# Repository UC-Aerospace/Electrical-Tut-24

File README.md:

# 2024 Avionics tutorial example boards!!
Here's where you'll find basic examples of a flight computer board using the RP2040 microcontroller. 

We have two different example sizes.  
  
(50mm x 50mm) This shows it's possible to design a 2-layer 50mm x 50mm board to fit the minimum rocket tube diameter of 50mm. Made by Grayson. This is the one we have ordered and will be avalible to pass around.  
  
~~(66mm x 66mm) This 2-layer example board is slightly bigger but small enough to fit in an L2 rocket. Made by Kaden.~~  
Unfortunatly this board has some issues at the moment, we might look into fixing it. Left for now as it shows a different general approach.

> [!NOTE]
> While making a 2-layer 50mm x 50mm board is possible, routing something this small can be quite a puzzle especially to do nicely. If you do target 50x50 we would reccomend a 4-layer board. Otherwise, we'd suggest something either 66x66mm or 88x88mm.

> [!CAUTION]
> We are not experts and are still all learning a lot ourselves. As such some of these designs may be suboptimal, don't take them as best practice. If you see an issue with any of the boards, or even just think you do, feel free to create an issue so we can all learn.

## Templates

These are barebones files to use as a starting point, and very simply include a board outline with holes that will match with our sleds, the RP2040 footprint and the Sense module footprint. Avalible in 50x50, 66x66 and 88x88 to modify as you wish.

## Resources / Datasheets
**_Please look_** at the datasheets for any major components you plan to use, e.g. (Voltage regulator, RP2040, Flash chip, Screen, LEDs, USB-C connector, etc..) They provide the information necessary to integrate them with your project and if any extra components are needed to work correctly.

The Raspberry Pi Foundation has provided a massive amount of technical information for the RP2040 microcontroller we use, so I'd suggest reviewing their datasheets to help build your boards! They definitely helped me :) 

[RP2040 Datasheet](https://datasheets.raspberrypi.com/rp2040/rp2040-datasheet.pdf)  
[RP2040 Hardware design examples](https://datasheets.raspberrypi.com/rp2040/hardware-design-with-rp2040.pdf)  
[Raspberry Pi Pico datasheet](https://datasheets.raspberrypi.com/pico/pico-datasheet.pdf)
  
Also take a look at the sensor package used which we have got assembled for you:
[MicroSense](https://github.com/UC-Aerospace/Sense)

If you have any questions about the example board, then come talk to me!  
Happy making! (The first year Grayson) :3

^ Graysons demo flight computer, we will have a few to pass around.

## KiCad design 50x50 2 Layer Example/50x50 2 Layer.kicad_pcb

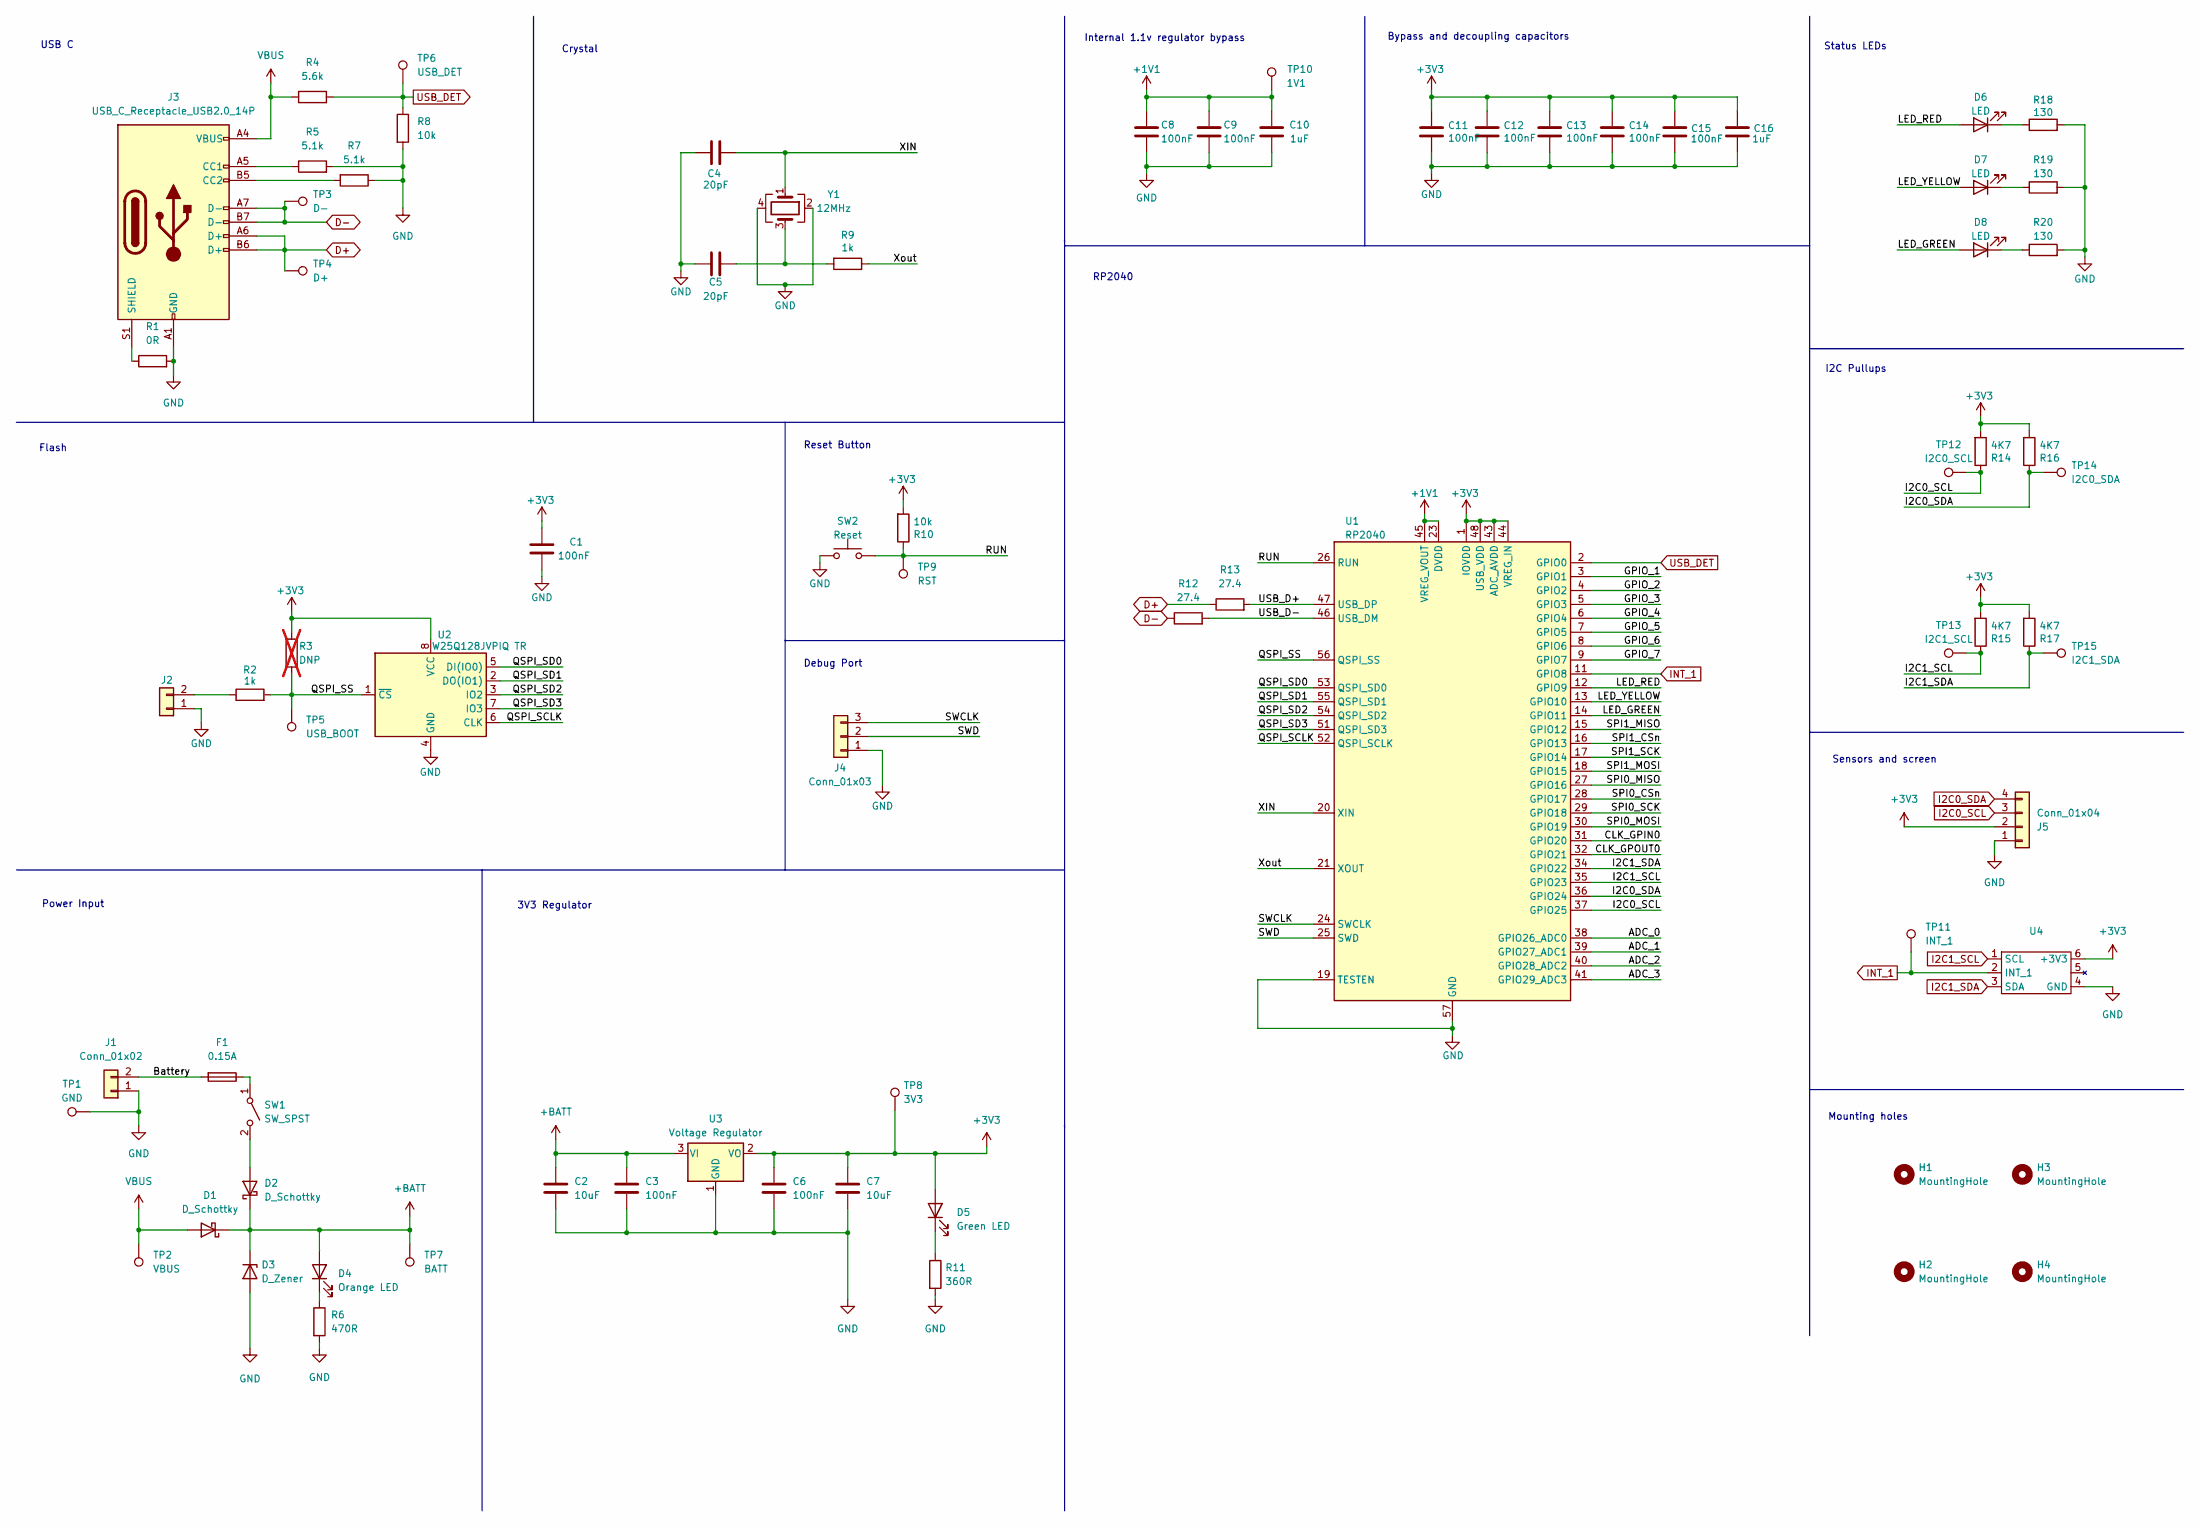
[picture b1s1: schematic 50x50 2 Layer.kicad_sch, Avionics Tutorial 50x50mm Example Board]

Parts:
C1, C8, C9, C11, C12, C13, C14: 100nF; C_0805_2012Metric_Pad1.18x1.45mm_HandSolder; MPN CL10B104KB8NNWC
C2, C7: 10uF; C_0805_2012Metric_Pad1.18x1.45mm_HandSolder; MPN CL21A106KOQNNNE
C3, C6: 100nF; C_0805_2012Metric_Pad1.18x1.45mm_HandSolder; MPN CL21B104KBCNNNC
C4, C5: 20pF; C_0805_2012Metric_Pad1.18x1.45mm_HandSolder; MPN 0603N270J500CT
C10, C16: 1uF; C_0805_2012Metric_Pad1.18x1.45mm_HandSolder; MPN CL10B105KA8NNNC
C15: 100nF; C_0805_2012Metric_Pad1.18x1.45mm_HandSolder; MPN CL10B105KA8NNNC
D1, D2: D_Schottky; D_SMA; MPN 4786-SK34ACT-ND
D3: D_Zener; D_SOD-123; MPN BZT52C12-TP
D4: Orange LED; LED_0603_1608Metric; MPN B1911UD--20D001014U1930
D5: Green LED; LED_0603_1608Metric; MPN B1931NG--20D001114U1930
D6: LED; LED_0402_1005Metric_Pad0.77x0.64mm_HandSolder; MPN 150040RS73240
D7: LED; LED_0402_1005Metric_Pad0.77x0.64mm_HandSolder; MPN 150040YS73240
D8: LED; LED_0402_1005Metric_Pad0.77x0.64mm_HandSolder; MPN 150040VS73240
F1: 0.15A; Fuse_0603_1608Metric; MPN FMC16302WHTP
H1, H2, H3, H4: MountingHole; MountingHole_3.2mm_M3
J1: Conn_01x02; JST_XH_B2B-XH-A_1x02_P2.50mm_Vertical; MPN S2B-XH-A(LF)(SN)
J2: Conn_01x02; PinHeader_1x02_P2.54mm_Vertical
J3: USB_C_Receptacle_USB2.0_14P; USB_C_Receptacle_GCT_USB4105-xx-A_16P_TopMnt_Horizontal
J4: Conn_01x03; PinSocket_1x03_P2.54mm_Vertical
J5: Conn_01x04; PinSocket_1x04_P2.54mm_Vertical
R1: 0R; R_0805_2012Metric_Pad1.20x1.40mm_HandSolder
R2, R9: 1k; R_0805_2012Metric_Pad1.20x1.40mm_HandSolder; MPN RMCF0603FT1K00
R3: DNP; R_0805_2012Metric_Pad1.20x1.40mm_HandSolder; not fitted
R4: 5.6k; R_0805_2012Metric_Pad1.20x1.40mm_HandSolder
R5, R7: 5.1k; R_0805_2012Metric_Pad1.20x1.40mm_HandSolder
R6: 470R; R_0805_2012Metric_Pad1.20x1.40mm_HandSolder; MPN RC0805JR-07360RL
R8: 10k; R_0805_2012Metric_Pad1.20x1.40mm_HandSolder
R10: 10k; R_0805_2012Metric_Pad1.20x1.40mm_HandSolder; MPN RMCF0603FT10K0
R11: 360R; R_0805_2012Metric_Pad1.20x1.40mm_HandSolder; MPN RC0805JR-07360RL
R12, R13: 27.4; R_0805_2012Metric_Pad1.20x1.40mm_HandSolder
R14, R15, R16, R17: 4K7; R_0805_2012Metric_Pad1.20x1.40mm_HandSolder; MPN RC0603FR-074K7L
R18, R19, R20: 130; R_0805_2012Metric_Pad1.20x1.40mm_HandSolder; MPN RC0603FR-07130RL
SW1: SW_SPST; JST_XH_B2B-XH-A_1x02_P2.50mm_Vertical; MPN S2B-XH-A(LF)(SN)
SW2: Reset; SW_SPST_PTS645; MPN PTS645SM43SMTR92 LFS
TP1: GND; TestPoint_Pad_1.0x1.0mm; MPN S1751-46R
TP2: VBUS; TestPoint_Pad_1.0x1.0mm; MPN S1751-46R
TP3: D-; TestPoint_Pad_1.0x1.0mm; MPN S1751-46R
TP4: D+; TestPoint_Pad_1.0x1.0mm; MPN S1751-46R
TP5: USB_BOOT; TestPoint_Pad_1.0x1.0mm; MPN S1751-46R
TP6: USB_DET; TestPoint_Pad_1.0x1.0mm; MPN S1751-46R
TP7: BATT; TestPoint_Pad_1.0x1.0mm; MPN S1751-46R
TP8: 3V3; TestPoint_Pad_1.0x1.0mm; MPN S1751-46R
TP9: RST; TestPoint_Pad_1.0x1.0mm; MPN S1751-46R
TP10: 1V1; TestPoint_Pad_1.0x1.0mm; MPN S1751-46R
TP11: INT_1; TestPoint_Pad_1.0x1.0mm; MPN S1751-46R
TP12: I2C0_SCL; TestPoint_Pad_1.0x1.0mm; MPN S1751-46R
TP13: I2C1_SCL; TestPoint_Pad_1.0x1.0mm; MPN S1751-46R
TP14: I2C0_SDA; TestPoint_Pad_1.0x1.0mm; MPN S1751-46R
TP15: I2C1_SDA; TestPoint_Pad_1.0x1.0mm; MPN S1751-46R
U1: RP2040; QFN-56-1EP_7x7mm_P0.4mm_EP3.2x3.2mm; MPN SC0914(13)
U2: W25Q128JVPIQ TR; SOIC-8_5.23x5.23mm_P1.27mm; MPN W25Q128JVPIQ TR
U3: Voltage Regulator; SOT-223; MPN BA033CC0FP-E2
U4: UCA_Sense
Y1: 12MHz; Crystal_SMD_3225-4Pin_3.2x2.5mm_HandSoldering

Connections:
+1V1: C8.1, C9.1, C10.2, TP10.1, U1.23 (DVDD), U1.45 (VREG_VOUT), U1.50 (DVDD)
+3V3: C1.2, C6.1, C7.1, C11.1, C12.1, C13.1, C14.1, C15.2, C16.2, D5.2 (A), J5.2, R3.1, R10.2, R14.2, R15.2, R16.2, R17.2, TP8.1, U1.1 (IOVDD), U1.10 (IOVDD), U1.22 (IOVDD), U1.33 (IOVDD), U1.42 (IOVDD), U1.43 (ADC_AVDD), U1.44 (VREG_IN), U1.48 (USB_VDD), U1.49 (IOVDD), U2.8 (VCC), U3.2 (VO), U4.6 (+3V3)
+BATT: C2.1, C3.1, D1.1 (K), D2.1 (K), D3.1 (K), D4.2 (A), TP7.1, U3.3 (VI)
/ADC_0: U1.38 (GPIO26_ADC0)
/ADC_1: U1.39 (GPIO27_ADC1)
/ADC_2: U1.40 (GPIO28_ADC2)
/ADC_3: U1.41 (GPIO29_ADC3)
/Battery: F1.2, J1.2
/CLK_GPIN0: U1.31 (GPIO20)
/CLK_GPOUT0: U1.32 (GPIO21)
/GPIO_1: U1.3 (GPIO1)
/GPIO_2: U1.4 (GPIO2)
/GPIO_3: U1.5 (GPIO3)
/GPIO_4: U1.6 (GPIO4)
/GPIO_5: U1.7 (GPIO5)
/GPIO_6: U1.8 (GPIO6)
/GPIO_7: U1.9 (GPIO7)
/LED_GREEN: D8.2 (A), U1.14 (GPIO11)
/LED_RED: D6.2 (A), U1.12 (GPIO9)
/LED_YELLOW: D7.2 (A), U1.13 (GPIO10)
/QSPI_SCLK: U1.52 (QSPI_SCLK), U2.6 (CLK)
/QSPI_SD0: U1.53 (QSPI_SD0), U2.5 (DI(IO0))
/QSPI_SD1: U1.55 (QSPI_SD1), U2.2 (DO(IO1))
/QSPI_SD2: U1.54 (QSPI_SD2), U2.3 (IO2)
/QSPI_SD3: U1.51 (QSPI_SD3), U2.7 (IO3)
/QSPI_SS: R2.2, R3.2, TP5.1, U1.56 (QSPI_SS), U2.1 (~CS)
/RUN: R10.1, SW2.2, TP9.1, U1.26 (RUN)
/SPI0_CSn: U1.28 (GPIO17)
/SPI0_MISO: U1.27 (GPIO16)
/SPI0_MOSI: U1.30 (GPIO19)
/SPI0_SCK: U1.29 (GPIO18)
/SPI1_CSn: U1.16 (GPIO13)
/SPI1_MISO: U1.15 (GPIO12)
/SPI1_MOSI: U1.18 (GPIO15)
/SPI1_SCK: U1.17 (GPIO14)
/SWCLK: J4.3, U1.24 (SWCLK)
/SWD: J4.2, U1.25 (SWD)
/USB_D+: R13.2, U1.47 (USB_DP)
/USB_D-: R12.2, U1.46 (USB_DM)
/XIN: C4.1, U1.20 (XIN), Y1.1
/Xout: R9.1, U1.21 (XOUT)
D+: J3.A6 (D+), J3.B6 (D+), R13.1, TP4.1
D-: J3.A7 (D-), J3.B7 (D-), R12.1, TP3.1
GND: C1.1, C2.2, C3.2, C4.2, C5.2, C6.2, C7.2, C8.2, C9.2, C10.1, C11.2, C12.2, C13.2, C14.2, C15.1, C16.1, D3.2 (A), J1.1, J2.1, J3.A1 (GND), J3.A12 (GND), J3.B1 (GND), J3.B12 (GND), J4.1, J5.1, R1.2, R5.2, R6.2, R7.1, R8.2, R11.2, R18.2, R19.2, R20.2, SW2.1, TP1.1, U1.19 (TESTEN), U1.57 (GND), U2.4 (GND), U3.1 (GND), U4.4 (GND), Y1.2, Y1.4
I2C0_SCL: J5.3, R14.1, TP12.1, U1.37 (GPIO25)
I2C0_SDA: J5.4, R16.1, TP14.1, U1.36 (GPIO24)
I2C1_SCL: R15.1, TP13.1, U1.35 (GPIO23), U4.1 (SCL)
I2C1_SDA: R17.1, TP15.1, U1.34 (GPIO22), U4.3 (SDA)
INT_1: TP11.1, U1.11 (GPIO8), U4.2 (INT_1)
unnamed: C5.1, R9.2, Y1.3
unnamed: D2.2 (A), SW1.2 (B)
unnamed: D4.1 (K), R6.1
unnamed: D5.1 (K), R11.1
unnamed: D6.1 (K), R18.1
unnamed: D7.1 (K), R19.1
unnamed: D8.1 (K), R20.1
unnamed: J2.2, R2.1
unnamed: J3.A5 (CC1), R5.1
unnamed: J3.B5 (CC2), R7.2
unnamed: J3.S1 (SHIELD), R1.1
unnamed: F1.1, SW1.1 (A)
USB_DET: R4.2, R8.1, TP6.1, U1.2 (GPIO0)
VBUS: D1.2 (A), J3.A4 (VBUS), J3.A9 (VBUS), J3.B4 (VBUS), J3.B9 (VBUS), R4.1, TP2.1

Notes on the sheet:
Sensors and screen
Debug Port
Mounting holes
Power Input
Crystal
I2C Pullups
Internal 1.1v regulator bypass
RP2040
3V3 Regulator
Flash
USB C
Status LEDs
Reset Button
Bypass and decoupling capacitors

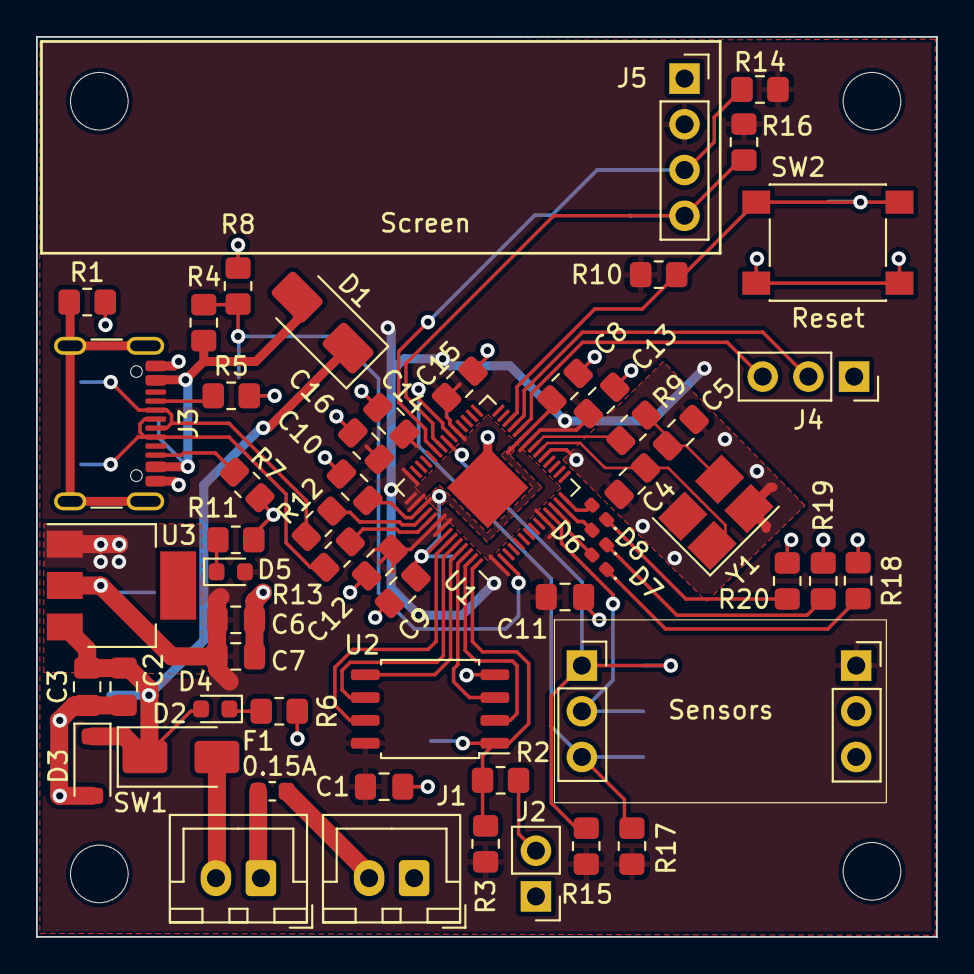
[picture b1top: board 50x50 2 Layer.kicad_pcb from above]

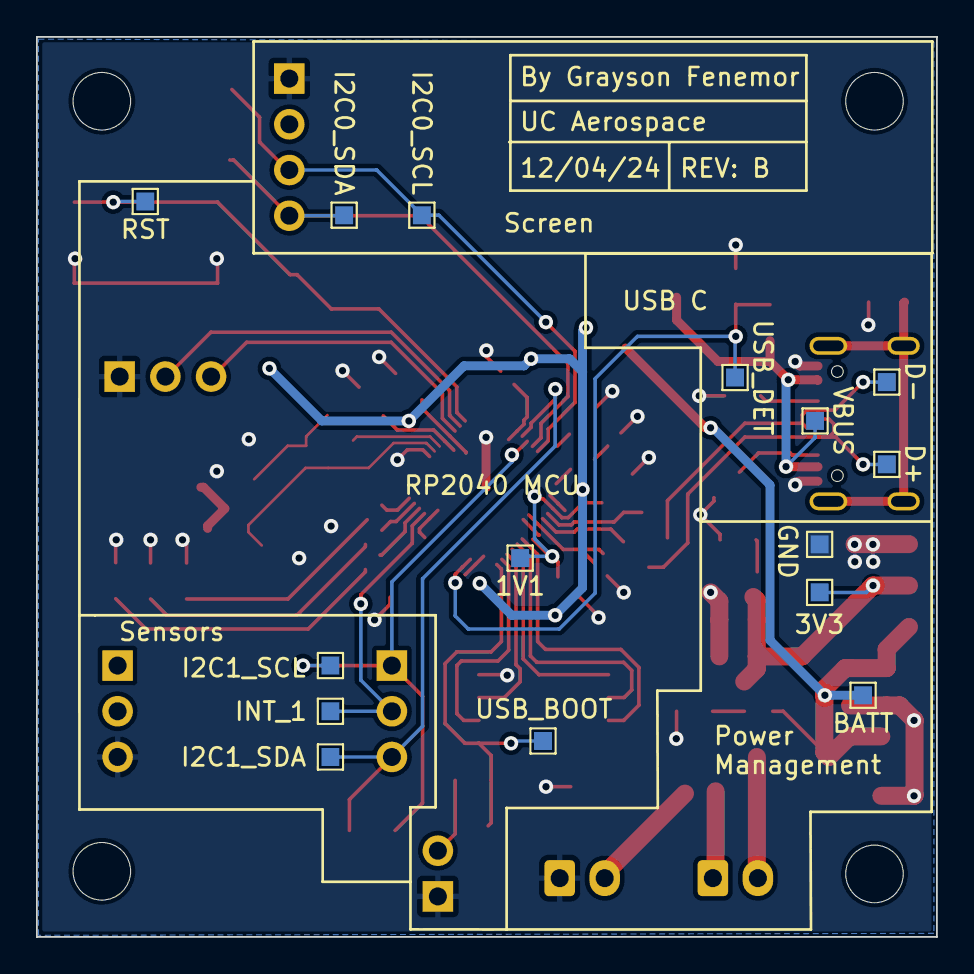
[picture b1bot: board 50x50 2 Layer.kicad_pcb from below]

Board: 2 copper layers, 50.0 x 50.0 mm, 76 parts (15 on the bottom side), 42 nets.

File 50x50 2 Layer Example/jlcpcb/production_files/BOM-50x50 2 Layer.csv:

Comment,Designator,Footprint,LCSC
470R,R6,R_0805_2012Metric_Pad1.20x1.40mm_HandSolder,C114564
LED,D6,LED_0402_1005Metric_Pad0.77x0.64mm_HandSolder,C136118
360R,R11,R_0805_2012Metric_Pad1.20x1.40mm_HandSolder,C137444
130,"R18,R19,R20",R_0805_2012Metric_Pad1.20x1.40mm_HandSolder,C137474
Conn_01x03,J4,PinSocket_1x03_P2.54mm_Vertical,C146243
0.15A,F1,Fuse_0603_1608Metric,C151137
Conn_01x02,"J1,SW1",JST_XH_B2B-XH-A_1x02_P2.50mm_Vertical,C158012
10uF,"C2,C7",C_0805_2012Metric_Pad1.18x1.45mm_HandSolder,C15850
10k,"R10,R8",R_0805_2012Metric_Pad1.20x1.40mm_HandSolder,C17414
0R,R1,R_0805_2012Metric_Pad1.20x1.40mm_HandSolder,C17477
1k,"R2,R9",R_0805_2012Metric_Pad1.20x1.40mm_HandSolder,C17513
27.4,"R12,R13",R_0805_2012Metric_Pad1.20x1.40mm_HandSolder,C17588
20pF,"C4,C5",C_0805_2012Metric_Pad1.18x1.45mm_HandSolder,C1798
RP2040,U1,QFN-56-1EP_7x7mm_P0.4mm_EP3.2x3.2mm,C2040
Orange LED,D4,LED_0603_1608Metric,C205445
LED,D7,LED_0402_1005Metric_Pad0.77x0.64mm_HandSolder,C264408
5.1k,"R5,R7",R_0805_2012Metric_Pad1.20x1.40mm_HandSolder,C27834
100nF,"C1,C11,C12,C13,C14,C15,C3,C6,C8,C9",C_0805_2012Metric_Pad1.18x1.45mm_HandSolder,C28233
1uF,"C10,C16",C_0805_2012Metric_Pad1.18x1.45mm_HandSolder,C28323
Reset,SW2,SW_SPST_PTS645,C2837531
D_Schottky,"D1,D2",D_SMA,C2909963
USB_C_Receptacle_USB2.0_14P,J3,USB_C_Receptacle_GCT_USB4105-xx-A_16P_TopMnt_Horizontal,C2988369
5.6k,R4,R_0805_2012Metric_Pad1.20x1.40mm_HandSolder,C4382
Conn_01x02,J2,PinHeader_1x02_P2.54mm_Vertical,C49661
12MHz,Y1,Crystal_SMD_3225-4Pin_3.2x2.5mm_HandSoldering,C50430
Conn_01x04,J5,PinSocket_1x04_P2.54mm_Vertical,C5116483
4K7,"R14,R15,R16,R17",R_0805_2012Metric_Pad1.20x1.40mm_HandSolder,C60816
Voltage Regulator,U3,SOT-223,C6186
D_Zener,D3,D_SOD-123,C668891
LED,D8,LED_0402_1005Metric_Pad0.77x0.64mm_HandSolder,C74339
Green LED,D5,LED_0603_1608Metric,C84264
W25Q128JVPIQ TR,U2,SOIC-8_5.23x5.23mm_P1.27mm,C97521

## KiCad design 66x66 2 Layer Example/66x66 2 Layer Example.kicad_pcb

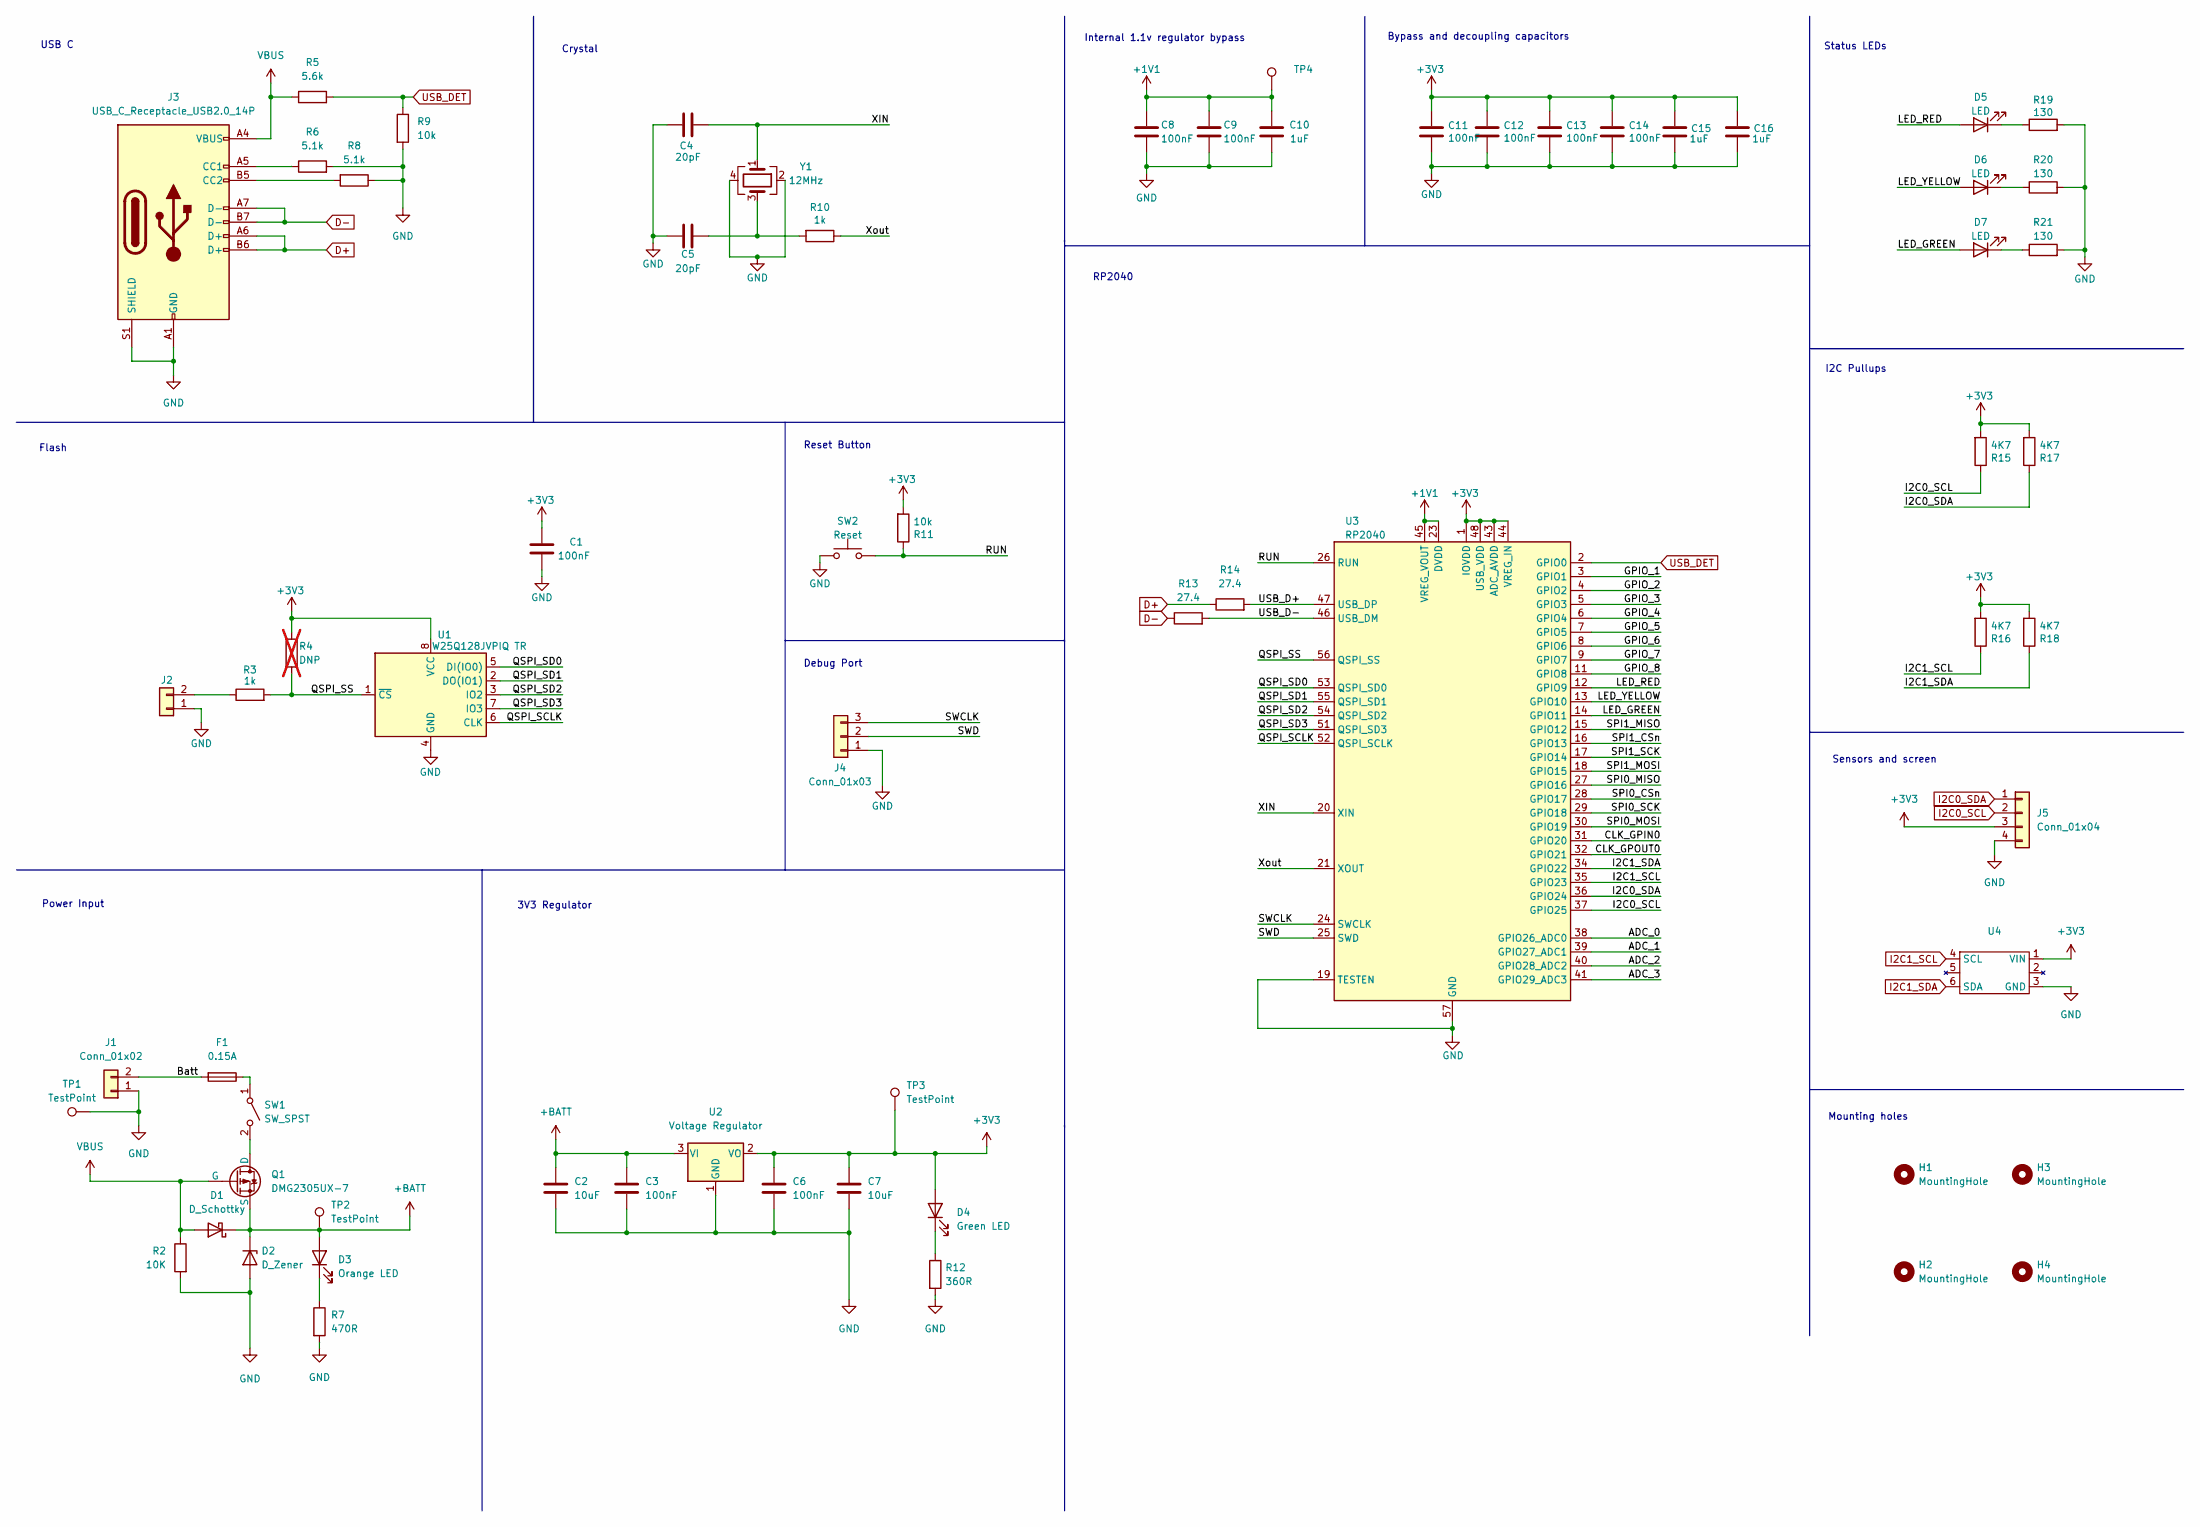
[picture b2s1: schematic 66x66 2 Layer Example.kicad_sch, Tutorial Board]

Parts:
C1, C8, C9, C11, C12, C13, C14: 100nF; C_0805_2012Metric_Pad1.18x1.45mm_HandSolder; MPN CL10B104KB8NNWC
C2, C7: 10uF; C_0805_2012Metric_Pad1.18x1.45mm_HandSolder; MPN CL21A106KOQNNNE
C3, C6: 100nF; C_0805_2012Metric_Pad1.18x1.45mm_HandSolder; MPN CL21B104KBCNNNC
C4, C5: 20pF; C_0805_2012Metric_Pad1.18x1.45mm_HandSolder; MPN 0603N270J500CT
C10, C15, C16: 1uF; C_0805_2012Metric_Pad1.18x1.45mm_HandSolder; MPN CL10B105KA8NNNC
D1: D_Schottky; D_SMA; MPN 4786-SK34ACT-ND
D2: D_Zener; D_SOD-123; MPN BZT52C12-TP
D3: Orange LED; LED_0603_1608Metric; MPN B1911UD--20D001014U1930
D4: Green LED; LED_0603_1608Metric; MPN B1931NG--20D001114U1930
D5: LED; LED_0402_1005Metric_Pad0.77x0.64mm_HandSolder; MPN 150040RS73240
D6: LED; LED_0402_1005Metric_Pad0.77x0.64mm_HandSolder; MPN 150040YS73240
D7: LED; LED_0402_1005Metric_Pad0.77x0.64mm_HandSolder; MPN 150040VS73240
F1: 0.15A; Fuse_0603_1608Metric; MPN FMC16302WHTP
H1, H2, H3, H4: MountingHole; MountingHole_3.2mm_M3
J1: Conn_01x02; JST_XH_B2B-XH-A_1x02_P2.50mm_Vertical; MPN S2B-XH-A(LF)(SN)
J2: Conn_01x02; PinSocket_1x02_P2.54mm_Vertical
J3: USB_C_Receptacle_USB2.0_14P; USB_C_Receptacle_GCT_USB4105-xx-A_16P_TopMnt_Horizontal
J4: Conn_01x03; PinSocket_1x03_P2.54mm_Vertical
J5: Conn_01x04; PinHeader_1x04_P2.54mm_Vertical
Q1: DMG2305UX-7; SOT-23_DIO
R2: 10K; R_0805_2012Metric_Pad1.20x1.40mm_HandSolder
R3, R10: 1k; R_0805_2012Metric_Pad1.20x1.40mm_HandSolder; MPN RMCF0603FT1K00
R4: DNP; R_0805_2012Metric_Pad1.20x1.40mm_HandSolder; not fitted
R5: 5.6k; R_0805_2012Metric_Pad1.20x1.40mm_HandSolder
R6, R8: 5.1k; R_0805_2012Metric_Pad1.20x1.40mm_HandSolder
R7: 470R; R_0805_2012Metric_Pad1.20x1.40mm_HandSolder; MPN RC0805JR-07360RL
R9: 10k; R_0805_2012Metric_Pad1.20x1.40mm_HandSolder
R11: 10k; R_0805_2012Metric_Pad1.20x1.40mm_HandSolder; MPN RMCF0603FT10K0
R12: 360R; R_0805_2012Metric_Pad1.20x1.40mm_HandSolder; MPN RC0805JR-07360RL
R13, R14: 27.4; R_0805_2012Metric_Pad1.20x1.40mm_HandSolder
R15, R16, R17, R18: 4K7; R_0805_2012Metric_Pad1.20x1.40mm_HandSolder; MPN RC0603FR-074K7L
R19, R20, R21: 130; R_0805_2012Metric_Pad1.20x1.40mm_HandSolder; MPN RC0603FR-07130RL
SW1: SW_SPST; JST_XH_B2B-XH-A_1x02_P2.50mm_Vertical; MPN S2B-XH-A(LF)(SN)
SW2: Reset; SW_SPST_PTS645; MPN PTS645SM43SMTR92 LFS
TP1, TP2, TP3: TestPoint; TestPoint_Pad_1.0x1.0mm; MPN S1751-46R
TP4: 1V1; TestPoint_Pad_1.0x1.0mm; MPN S1751-46R
U1: W25Q128JVPIQ TR; SOIC-8_5.23x5.23mm_P1.27mm; MPN W25Q128JVPIQ TR
U2: Voltage Regulator; SOT-223; MPN BA033CC0FP-E2
U3: RP2040; QFN-56-1EP_7x7mm_P0.4mm_EP3.2x3.2mm; MPN SC0914(13)
U4: SenseBoard
Y1: 12MHz; Crystal_SMD_3225-4Pin_3.2x2.5mm_HandSoldering

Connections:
+1V1: C8.1, C9.1, C10.2, TP4.1, U3.23 (DVDD), U3.45 (VREG_VOUT), U3.50 (DVDD)
+3V3: C1.2, C6.1, C7.1, C11.1, C12.1, C13.1, C14.1, C15.2, C16.2, D4.2 (A), J5.3, R4.1, R11.2, R15.2, R16.2, R17.2, R18.2, TP3.1, U1.8 (VCC), U2.2 (VO), U3.1 (IOVDD), U3.10 (IOVDD), U3.22 (IOVDD), U3.33 (IOVDD), U3.42 (IOVDD), U3.43 (ADC_AVDD), U3.44 (VREG_IN), U3.48 (USB_VDD), U3.49 (IOVDD), U4.1 (VIN)
+BATT: C2.1, C3.1, D1.1 (K), D2.1 (K), D3.2 (A), Q1.3 (S), TP2.1, U2.3 (VI)
/ADC_0: U3.38 (GPIO26_ADC0)
/ADC_1: U3.39 (GPIO27_ADC1)
/ADC_2: U3.40 (GPIO28_ADC2)
/ADC_3: U3.41 (GPIO29_ADC3)
/Batt: F1.2, J1.2
/CLK_GPIN0: U3.31 (GPIO20)
/CLK_GPOUT0: U3.32 (GPIO21)
/GPIO_1: U3.3 (GPIO1)
/GPIO_2: U3.4 (GPIO2)
/GPIO_3: U3.5 (GPIO3)
/GPIO_4: U3.6 (GPIO4)
/GPIO_5: U3.7 (GPIO5)
/GPIO_6: U3.8 (GPIO6)
/GPIO_7: U3.9 (GPIO7)
/GPIO_8: U3.11 (GPIO8)
/LED_GREEN: D7.2 (A), U3.14 (GPIO11)
/LED_RED: D5.2 (A), U3.12 (GPIO9)
/LED_YELLOW: D6.2 (A), U3.13 (GPIO10)
/QSPI_SCLK: U1.6 (CLK), U3.52 (QSPI_SCLK)
/QSPI_SD0: U1.5 (DI(IO0)), U3.53 (QSPI_SD0)
/QSPI_SD1: U1.2 (DO(IO1)), U3.55 (QSPI_SD1)
/QSPI_SD2: U1.3 (IO2), U3.54 (QSPI_SD2)
/QSPI_SD3: U1.7 (IO3), U3.51 (QSPI_SD3)
/QSPI_SS: R3.2, R4.2, U1.1 (~CS), U3.56 (QSPI_SS)
/RUN: R11.1, SW2.2, U3.26 (RUN)
/SPI0_CSn: U3.28 (GPIO17)
/SPI0_MISO: U3.27 (GPIO16)
/SPI0_MOSI: U3.30 (GPIO19)
/SPI0_SCK: U3.29 (GPIO18)
/SPI1_CSn: U3.16 (GPIO13)
/SPI1_MISO: U3.15 (GPIO12)
/SPI1_MOSI: U3.18 (GPIO15)
/SPI1_SCK: U3.17 (GPIO14)
/SWCLK: J4.3, U3.24 (SWCLK)
/SWD: J4.2, U3.25 (SWD)
/USB_D+: R14.2, U3.47 (USB_DP)
/USB_D-: R13.2, U3.46 (USB_DM)
/XIN: C4.1, U3.20 (XIN), Y1.1
/Xout: R10.1, U3.21 (XOUT)
D+: J3.A6 (D+), J3.B6 (D+), R14.1
D-: J3.A7 (D-), J3.B7 (D-), R13.1
GND: C1.1, C2.2, C3.2, C4.2, C5.2, C6.2, C7.2, C8.2, C9.2, C10.1, C11.2, C12.2, C13.2, C14.2, C15.1, C16.1, D2.2 (A), J1.1, J2.1, J3.A1 (GND), J3.A12 (GND), J3.B1 (GND), J3.B12 (GND), J3.S1 (SHIELD), J4.1, J5.4, R2.2, R6.2, R7.2, R8.1, R9.2, R12.2, R19.2, R20.2, R21.2, SW2.1, TP1.1, U1.4 (GND), U2.1 (GND), U3.19 (TESTEN), U3.57 (GND), U4.3 (GND), Y1.2, Y1.4
I2C0_SCL: J5.2, R15.1, U3.37 (GPIO25)
I2C0_SDA: J5.1, R17.1, U3.36 (GPIO24)
I2C1_SCL: R16.1, U3.35 (GPIO23), U4.4 (SCL)
I2C1_SDA: R18.1, U3.34 (GPIO22), U4.6 (SDA)
unnamed: C5.1, R10.2, Y1.3
unnamed: D3.1 (K), R7.1
unnamed: D4.1 (K), R12.1
unnamed: D5.1 (K), R19.1
unnamed: D6.1 (K), R20.1
unnamed: D7.1 (K), R21.1
unnamed: J2.2, R3.1
unnamed: J3.A5 (CC1), R6.1
unnamed: J3.B5 (CC2), R8.2
unnamed: Q1.1 (D), SW1.2 (B)
unnamed: F1.1, SW1.1 (A)
USB_DET: R5.2, R9.1, U3.2 (GPIO0)
VBUS: D1.2 (A), J3.A4 (VBUS), J3.A9 (VBUS), J3.B4 (VBUS), J3.B9 (VBUS), Q1.2 (G), R2.1, R5.1

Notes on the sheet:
Sensors and screen
Debug Port
Mounting holes
Power Input
Crystal
I2C Pullups
Internal 1.1v regulator bypass
RP2040
3V3 Regulator
Flash
USB C
Status LEDs
Reset Button
Bypass and decoupling capacitors

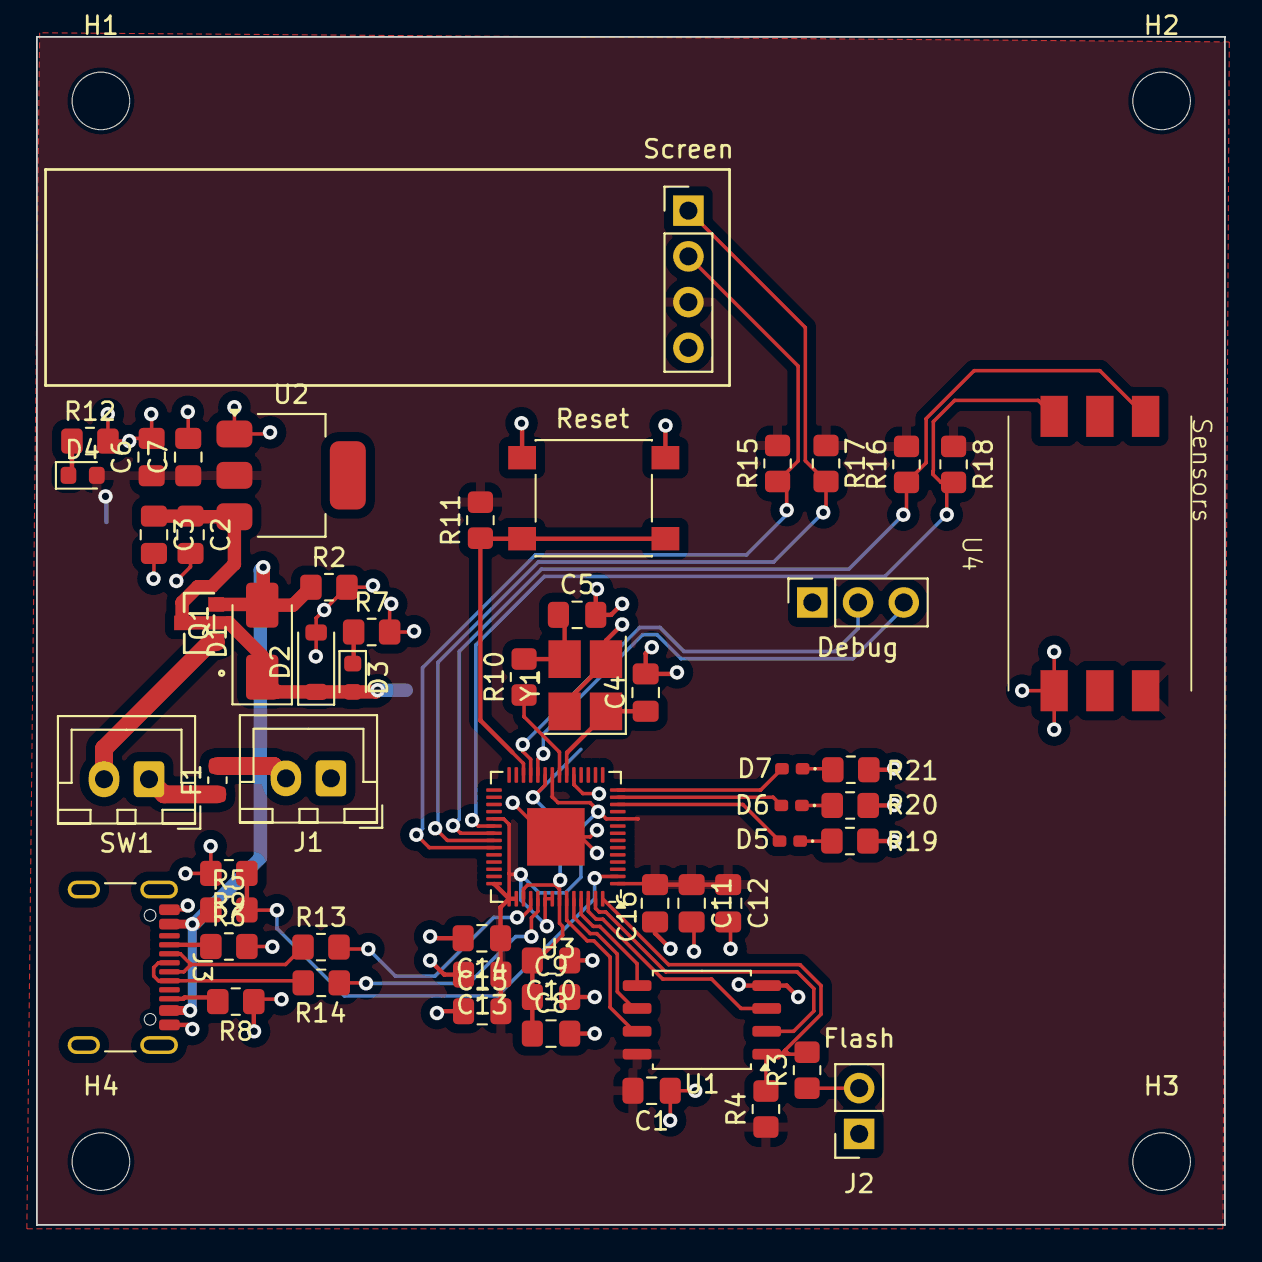
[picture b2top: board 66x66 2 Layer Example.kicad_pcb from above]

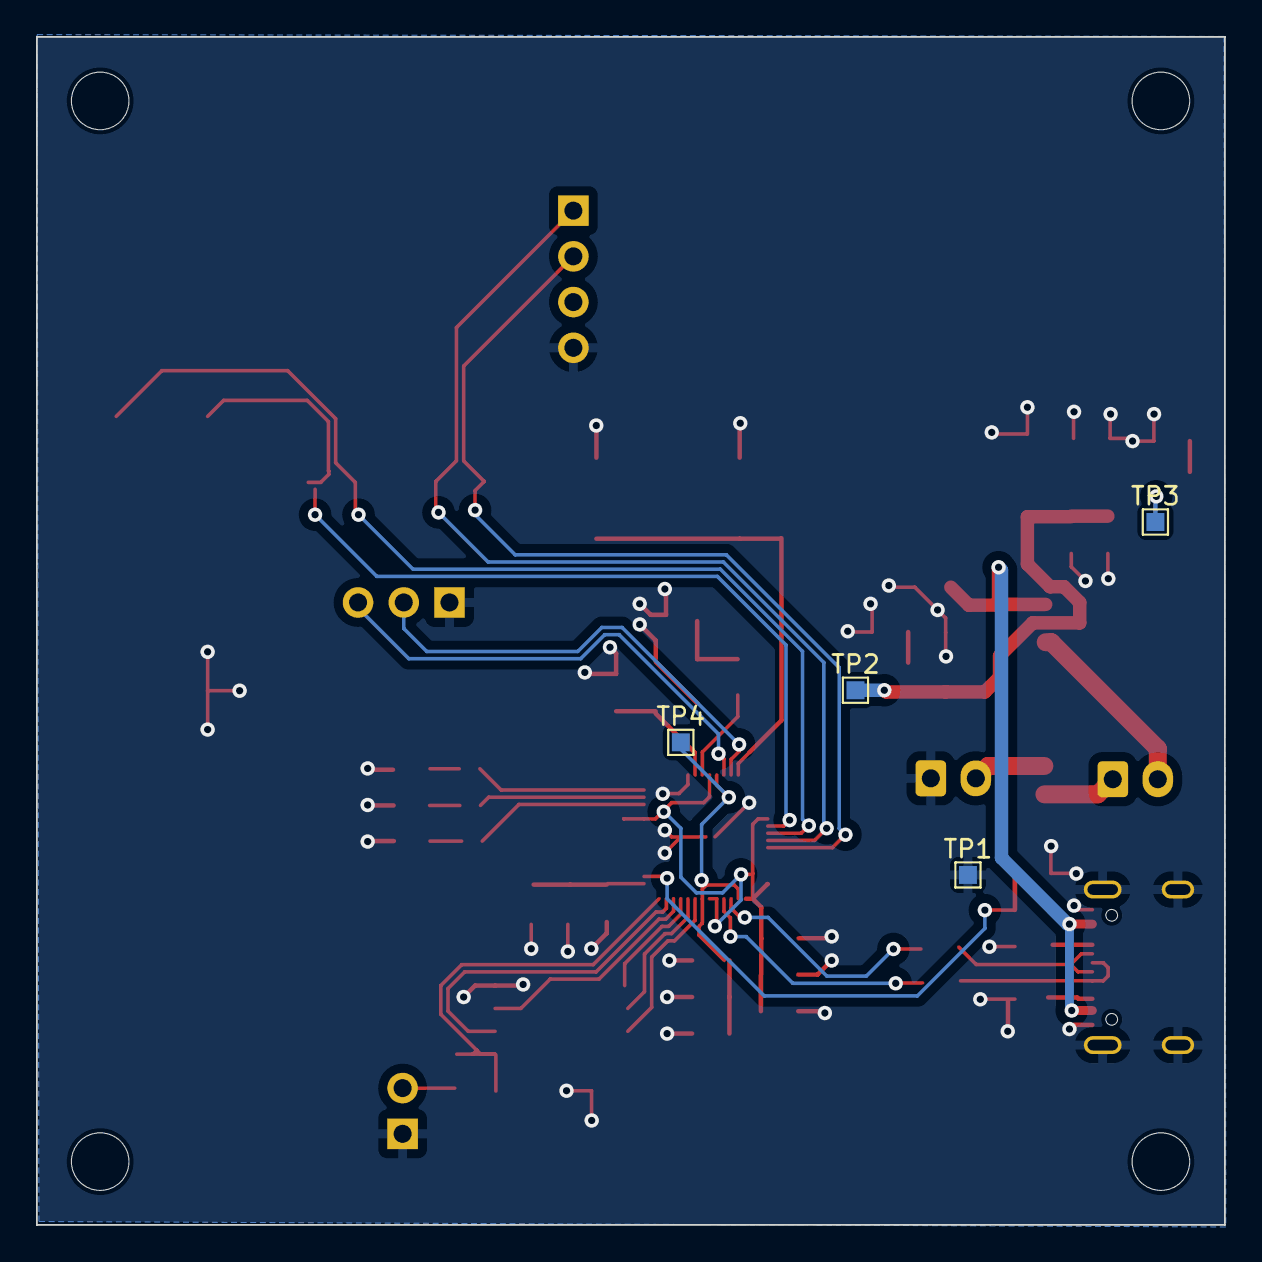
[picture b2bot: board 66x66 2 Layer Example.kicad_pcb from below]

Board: 2 copper layers, 66.0 x 66.0 mm, 65 parts (4 on the bottom side), 40 nets.

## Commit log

2024-04-03 Initial
2024-04-03 Relocated the example
2024-04-10 Updated Schematic
2024-04-11 Added 66x66 Board
2024-04-11 Added sense footprint
2024-04-12 Added 3d model
2024-04-12 Updated 66x66 to fix Clarence issues. Minimum 0.2mm
2024-04-12 Updated board and schematic
    PCB and schematic have been updated to REV B
2024-04-12 Added 3D model for sense
2024-04-12 Fixed screen connector and tidied GND plane
    The OLED screen connector was flipped, so fixed that. Tidied up some long GND paths as well.
2024-04-17 Created BOM with LCSC components Linked BOM to Schematic Generated Production Files for JLCPCB
2024-04-28 Added template boards
2024-05-11 Updated Template, to give more of an Outline
2024-05-11 To be reviewed
2024-05-11 Nuke 66x66 2 Layer Example
    Several critical issues have rendered this one more of a hinderance than its worth. If you've referenced this design please carefully check that your Sense and screen footprints align with the other 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
